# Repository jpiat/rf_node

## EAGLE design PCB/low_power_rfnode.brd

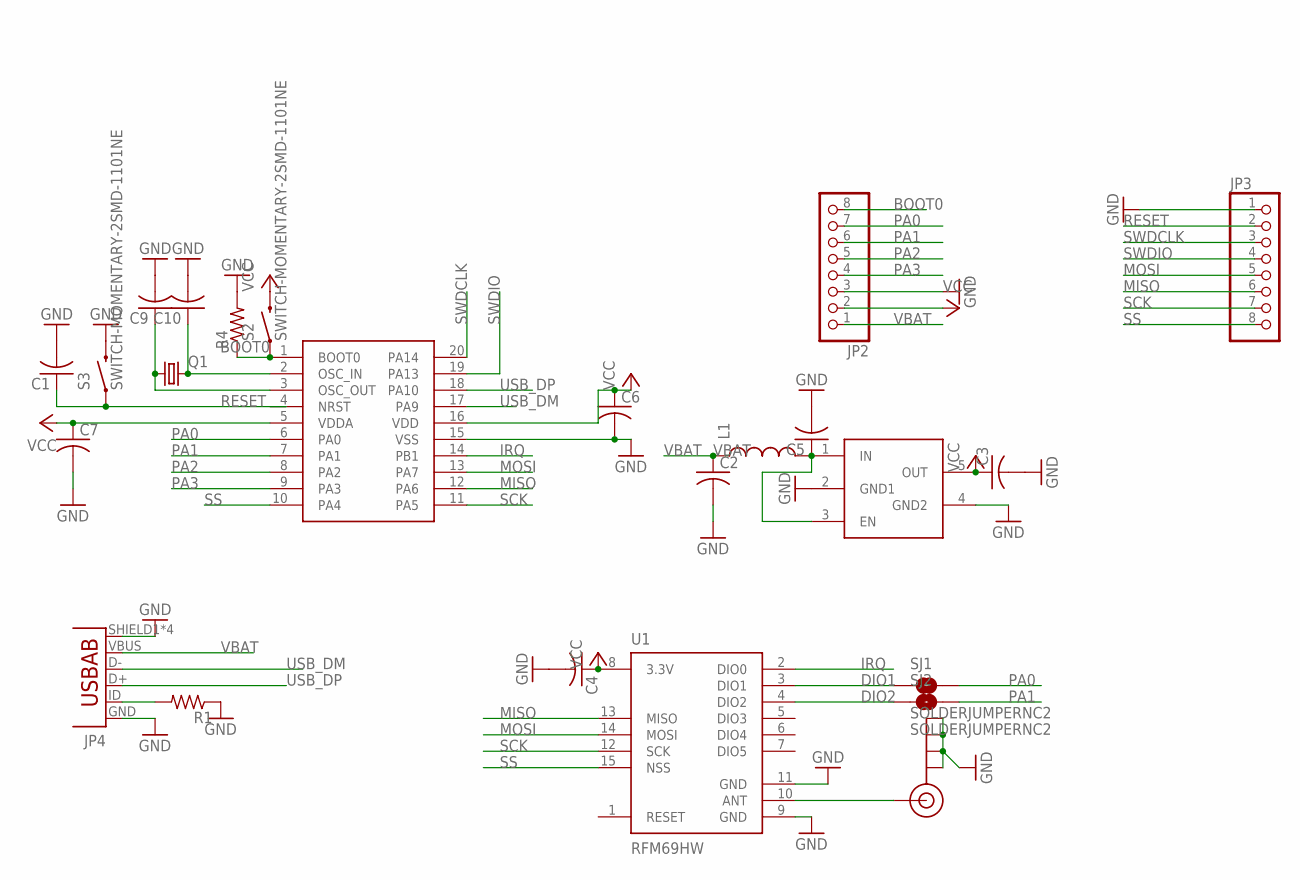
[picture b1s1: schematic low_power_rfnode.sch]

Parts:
C1, C2, C3, C4, C5, C6, C7, C9, C10: C-USC0805K; C0805K
J1: SMA_EDGE; SMA-EDGE
JP2, JP3: PINHD-1X8BIG; 1X08-BIG
JP4: USB-AB; USB-AB-MICRO-SMD
L1: INDUCTOR0805; 0805
Q1: CRYSTALHC49S; HC49/S
R1, R4: R-US_R0805; R0805
REG: TPS783; SOT23-5
S2, S3: SWITCH-MOMENTARY-2SMD-1101NE; TACTILE-SWITCH-1101NE
SJ1, SJ2: SOLDERJUMPERNC2; SJ_2S-NOTRACE
U1: RFM69HW; RFM69W-XXXS2
U$1: STM32F0; TSSOP20

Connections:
BOOT0: JP2.8, R4.1, S2.1, U$1.1 (BOOT0)
DIO1: SJ1.1, U1.3 (DIO1)
DIO2: SJ2.1, U1.4 (DIO2)
GND: C1.2, C2.2, C3.2, C4.2, C5.2, C6.2, C7.2, C9.2, C10.2, J1.GND@0 (GND), J1.GND@1 (GND), J1.GND@2 (GND), J1.GND@3 (GND), JP2.3, JP3.1, JP4.GND, JP4.SHIELD1 (SHIELD), JP4.SHIELD2 (SHIELD), JP4.SHIELD3 (SHIELD), JP4.SHIELD4 (SHIELD), R1.1, R4.2, REG.2 (GND1), REG.4 (GND2), S3.2, U1.9 (GND), U1.11 (GND), U$1.15 (VSS)
IRQ: U1.2 (DIO0), U$1.14 (PB1)
MISO: JP3.6, U1.13 (MISO), U$1.12 (PA6)
MOSI: JP3.5, U1.14 (MOSI), U$1.13 (PA7)
unnamed: C10.1, Q1.2, U$1.2 (OSC_IN)
unnamed: JP4.ID (USBID), R1.2
unnamed: C9.1, Q1.1, U$1.3 (OSC_OUT)
unnamed: C5.1, L1.2, REG.1 (IN), REG.3 (EN)
unnamed: J1.SIG (SIGNAL), U1.10 (ANT)
PA0: JP2.7, SJ1.2, U$1.6 (PA0)
PA1: JP2.6, SJ2.2, U$1.7 (PA1)
PA2: JP2.5, U$1.8 (PA2)
PA3: JP2.4, U$1.9 (PA3)
RESET: C1.1, JP3.2, S3.1, U$1.4 (NRST)
SCK: JP3.7, U1.12 (SCK), U$1.11 (PA5)
SS: JP3.8, U1.15 (NSS), U$1.10 (PA4)
SWDCLK: JP3.3, U$1.20 (PA14)
SWDIO: JP3.4, U$1.19 (PA13)
USB_DM: JP4.D-, U$1.17 (PA9)
USB_DP: JP4.D+, U$1.18 (PA10)
VBAT: C2.1, JP2.1, JP4.VBUS, L1.1
VCC: C3.1, C4.1, C6.1, C7.1, JP2.2, REG.5 (OUT), S2.2, U1.8 (3.3V), U$1.5 (VDDA), U$1.16 (VDD)

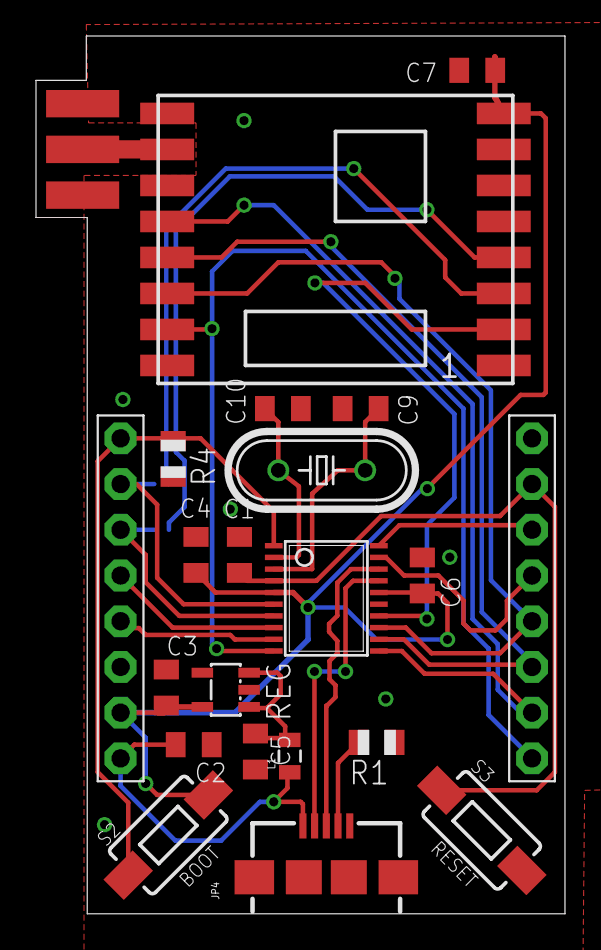
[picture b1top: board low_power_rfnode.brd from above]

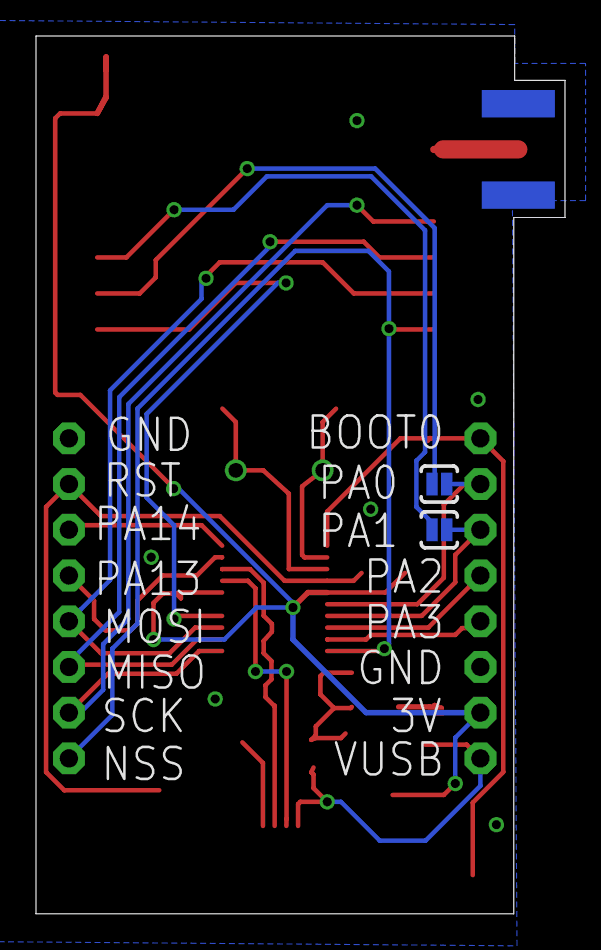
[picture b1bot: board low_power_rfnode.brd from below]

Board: 2 copper layers, 29.4 x 48.8 mm, 24 parts (2 on the bottom side), 25 nets.

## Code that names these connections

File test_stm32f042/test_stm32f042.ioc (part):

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Mcu.Name=STM32F042F6Px
Mcu.Package=TSSOP20
Mcu.UserName=STM32F042F6Px
PA0.Signal=GPIO_Output
PA11.Mode=Device
PA11.Signal=USB_DM
PA12.Mode=Device
PA12.Signal=USB_DP
PA4.Mode=NSS_Signal_Hard_Output
PA4.Signal=SPI1_NSS
PA5.Mode=Full_Duplex_Master
PA5.Signal=SPI1_SCK
PA6.Mode=Full_Duplex_Master
PA6.Signal=SPI1_MISO
PA7.Mode=Full_Duplex_Master
PA7.Signal=SPI1_MOSI
PB1.Signal=GPXTI1
RCC.SYSCLKFreq_VALUE=48000000
RCC.SYSCLKSource=RCC_SYSCLKSOURCE_HSI48
board=test_stm32f042

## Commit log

2016-05-30 Adding gitignore file
2016-05-30 Initial push for the test project for stm32f042
2016-05-30 Added PCB design

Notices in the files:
parts and their libraries:
SparkFun-Connectors: Licensing: Creative Commons ShareAlike 4.0 International - https://creativecommons.org/licenses/by-sa/4.0
